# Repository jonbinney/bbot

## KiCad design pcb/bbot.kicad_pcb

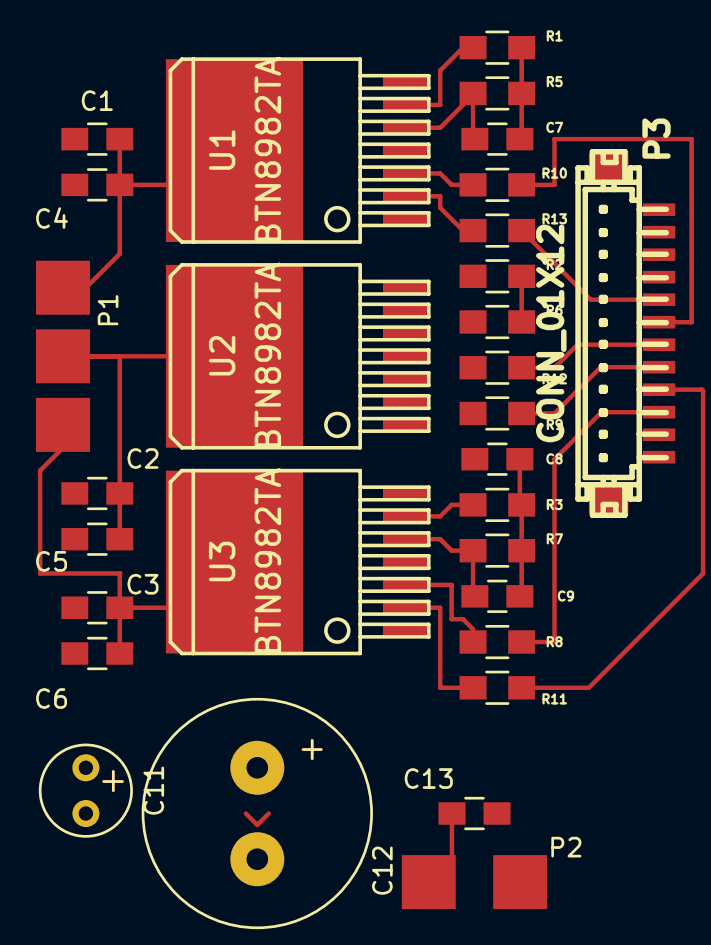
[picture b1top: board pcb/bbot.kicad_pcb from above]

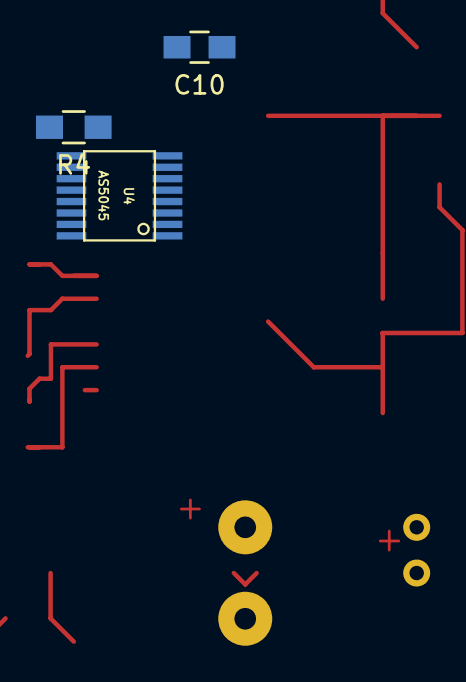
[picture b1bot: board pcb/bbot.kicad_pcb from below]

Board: 2 copper layers, 33 parts (3 on the bottom side), 29 nets.

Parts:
C1, C2, C3, C4, C5, C6: 220nF; C_0805_HandSoldering
C7, C8, C9, C10, C13: 100nF; C_0805_HandSoldering
C11: 5uF; Elko_vert_11x5mm_RM2.5
C12: 1000uF; Elko_vert_25x12.5mm_RM5
P1: CONN_01X03; JDB_BLDC_CONN
P2: CONN_01X02; JDB_BATT_CONN
P3: CONN_01X12; df13c-12p-125v
R1, R2, R3: 1k; R_0805_HandSoldering
R4, R8, R9, R10, R11, R12, R13: 10k; R_0805_HandSoldering
R5, R6, R7: 0.51k; R_0805_HandSoldering
U1, U2, U3: BTN8982TA; TO263-7
U4: AS5045; ssop-16

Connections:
+5V: C10.2, P3.12, R4.2, U4.16
GND: C1.1, C2.1, C3.1, C7.2, C8.2, C9.2, C10.1, C11.2, C12.2, C13.2, P2.2, P3.1, R1.2, R2.2, R3.2, R5.2, R6.2, R7.2, U1.1, U2.1, U3.1, U4.7
INH_A: R10.2, U1.3
INH_B: R9.2, U2.3
INH_C: R8.2, U3.3
IN_A: R13.2, U1.2
IN_B: R12.2, U2.2
IN_C: R11.2, U3.2
MOTOR_OUT_A: C1.2, C4.2, P1.1, U1.4
MOTOR_OUT_B: C2.2, C5.2, P1.2, U2.4
MOTOR_OUT_C: C3.2, C6.2, P1.3, U3.4
unnamed: C11.1, U4.15
unnamed: P3.5, R13.1
unnamed: P3.6, R10.1
unnamed: P3.7, R12.1
unnamed: P3.8, R9.1
unnamed: P3.9, R11.1
unnamed: P3.10, R8.1
unnamed: R1.1, U1.6
unnamed: R2.1, U2.6
unnamed: R3.1, U3.6
unnamed: R4.1, U4.6
SPI_CLK: P3.3, U4.10
SPI_CS: P3.4, U4.11
SPI_MISO: P3.2, U4.9
SR_A: C7.1, R5.1, U1.5
SR_B: C8.1, R6.1, U2.5
SR_C: C9.1, R7.1, U3.5
VCC: C4.1, C5.1, C6.1, C12.1, C13.1, P2.1, U1.7, U2.7, U3.7

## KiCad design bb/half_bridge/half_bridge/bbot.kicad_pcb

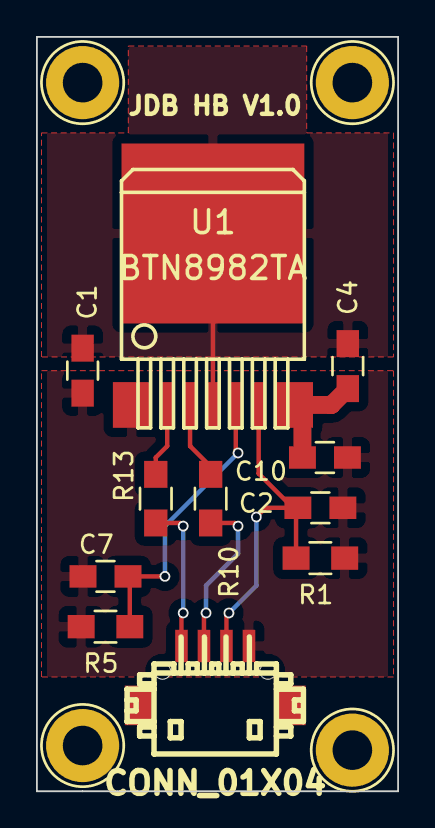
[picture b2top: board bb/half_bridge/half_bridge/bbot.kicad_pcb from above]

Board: 2 copper layers, 20.1 x 41.9 mm, 11 parts (0 on the bottom side), 9 nets.

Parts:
C1, C4: 220nF; C_0805_HandSoldering
C2: 1nF; C_0805_HandSoldering
C7, C10: 100nF; C_0805_HandSoldering
P3: CONN_01X04; df13-4p-125h
R1: 1k; R_0805_HandSoldering
R5: 0.51k; R_0805_HandSoldering
R10, R13: 10k; R_0805_HandSoldering
U1: BTN8982TA; BTN8982

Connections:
GND: C1.1, C2.2, C7.2, C10.2, P3.1, R1.2, R5.2, U1.1
IN: R13.2, U1.2
INH: R10.2, U1.3
IS: C2.1, P3.2, R1.1, U1.6
MOTOR_OUT: C1.2, C4.2, U1.4
unnamed: P3.3, R10.1
unnamed: P3.4, R13.1
SR: C7.1, R5.1, U1.5
VCC: C4.1, C10.1, U1.7

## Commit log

2015-08-23 SPI comms with AS5045 encoder work
2015-08-27 Move firmware to subdirectory
2015-08-27 Schematic done for rev1
2015-08-30 Submitted half bridge v1.0 for fab
    Sent to oshpark.
2015-08-30 Move half bridge pcb into its own directory
2015-09-08 Added experimental PWM output to bbot firmware
2015-10-24 Update firwmare for cmake (px4 switched)
2015-10-24 Firmware integrates gyro to get yaw
2015-10-24 CAD for motor mount
2016-01-28 CAD for invertible spinner
2016-02-16 Almost done with C-dinosaur
2016-02-18 Tweaks to cad
2016-02-22 Version that fought at fetch on Feb 20, 2016
2016-03-06 Separate directory for each bot
2016-03-26 Ignore solidworks temp files
2016-03-26 Start determined diplodocus (DD)
2016-10-23 Startig dug firmware
2016-10-23 Motor acceleration test
2019-05-26 Add vscode+pio project for ee battlebot
    This is planned to be a melty brain style bot for the aug 3 wpfl.
2019-05-28 SPI ADC works on breadboard
